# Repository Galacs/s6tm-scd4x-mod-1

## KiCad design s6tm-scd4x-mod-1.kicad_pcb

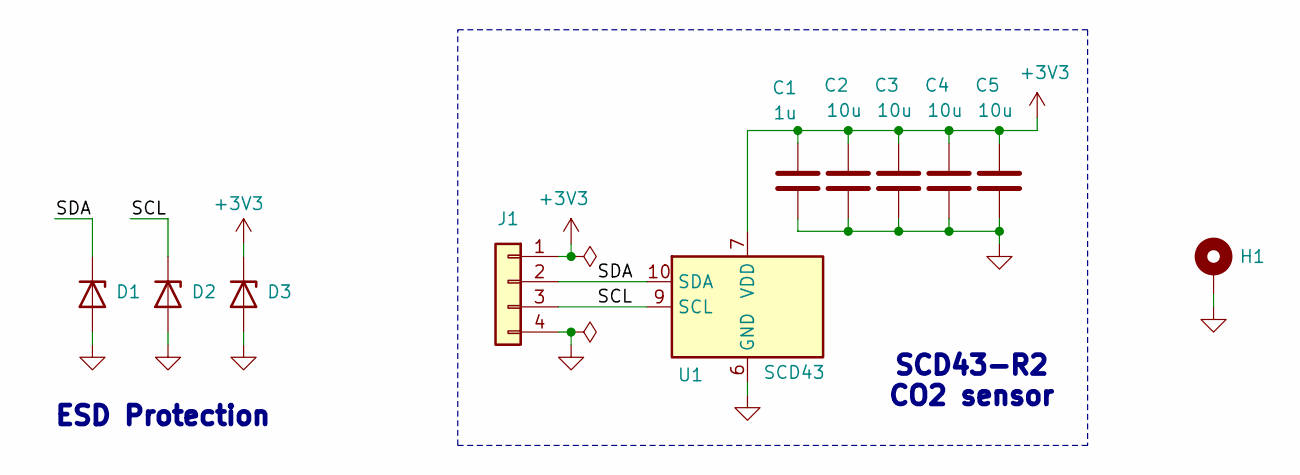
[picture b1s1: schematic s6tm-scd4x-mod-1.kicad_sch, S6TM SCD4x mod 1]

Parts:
C1: 1u; C_0402_1005Metric; Manufacturer Part Number CL05A105KA5NQNC; JLCPCB Part # C52923
C2, C3, C4, C5: 10u; C_0603_1608Metric; Manufacturer Part Number CL10A106KP8NNNC; JLCPCB Part # C19702
D1, D2, D3: H5VU10U; Diode_DFN1006; Manufacturer Part Number H5VU10U; JLCPCB Part # C22395519
H1: MountingHole_Pad; MountingHole_2.2mm_M2_Pad_Via
J1: Conn_01x04; PinHeader_1x04_P2.54mm_Vertical
U1: SCD43; Sensirion_SCD4x-1EP_10.1x10.1mm_P1.25mm_EP4.8x4.8mm; Manufacturer Part Number SCD43-D-R2; JLCPCB Part # C50182965

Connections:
+3V3: C1.2, C2.1, C3.1, C4.1, C5.1, D3.1 (K), J1.1, U1.7 (VDD), U1.19 (VDD)
/SCL: D2.1 (K), J1.3, U1.9 (SCL)
/SDA: D1.1 (K), J1.2, U1.10 (SDA)
GND: C1.1, C2.2, C3.2, C4.2, C5.2, D1.2 (A), D2.2 (A), D3.2 (A), H1.1 (1_1), J1.4, U1.6 (GND), U1.20 (GND), U1.21 (GND)

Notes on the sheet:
ESD Protection
SCD43-R2 CO2 sensor

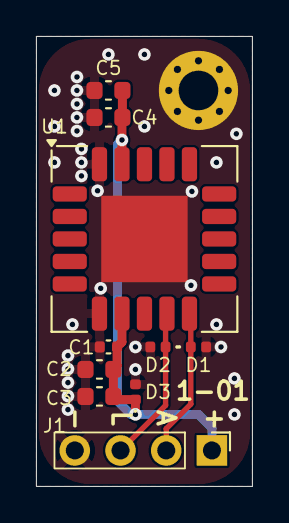
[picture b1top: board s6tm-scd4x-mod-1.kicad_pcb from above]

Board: 2 copper layers, 12.0 x 25.0 mm, 11 parts (0 on the bottom side), 4 nets.

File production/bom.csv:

Designator,Footprint,Quantity,Value,LCSC Part #
C1,0402,1,1u,C52923
"C2, C3, C4, C5",0603,4,10u,C19702
"D1, D2, D3",Diode_DFN1006,3,H5VU10U,C22395519
U1,Sensirion_SCD4x-1EP_10.1x10.1mm_P1.25mm_EP4.8x4.8mm,1,SCD43,C50182965

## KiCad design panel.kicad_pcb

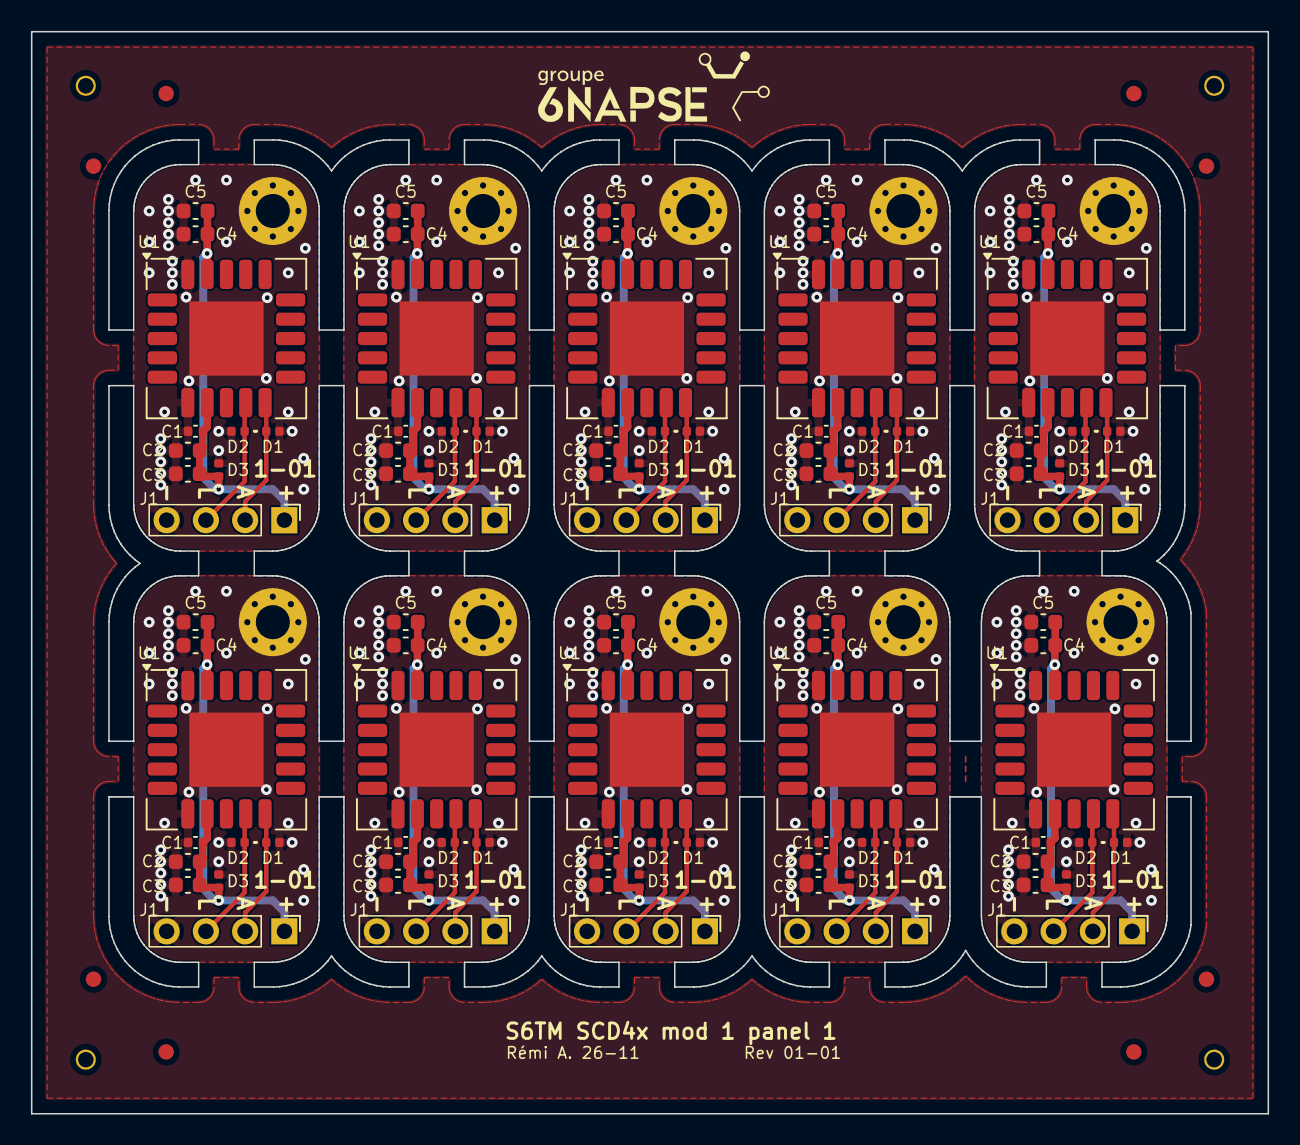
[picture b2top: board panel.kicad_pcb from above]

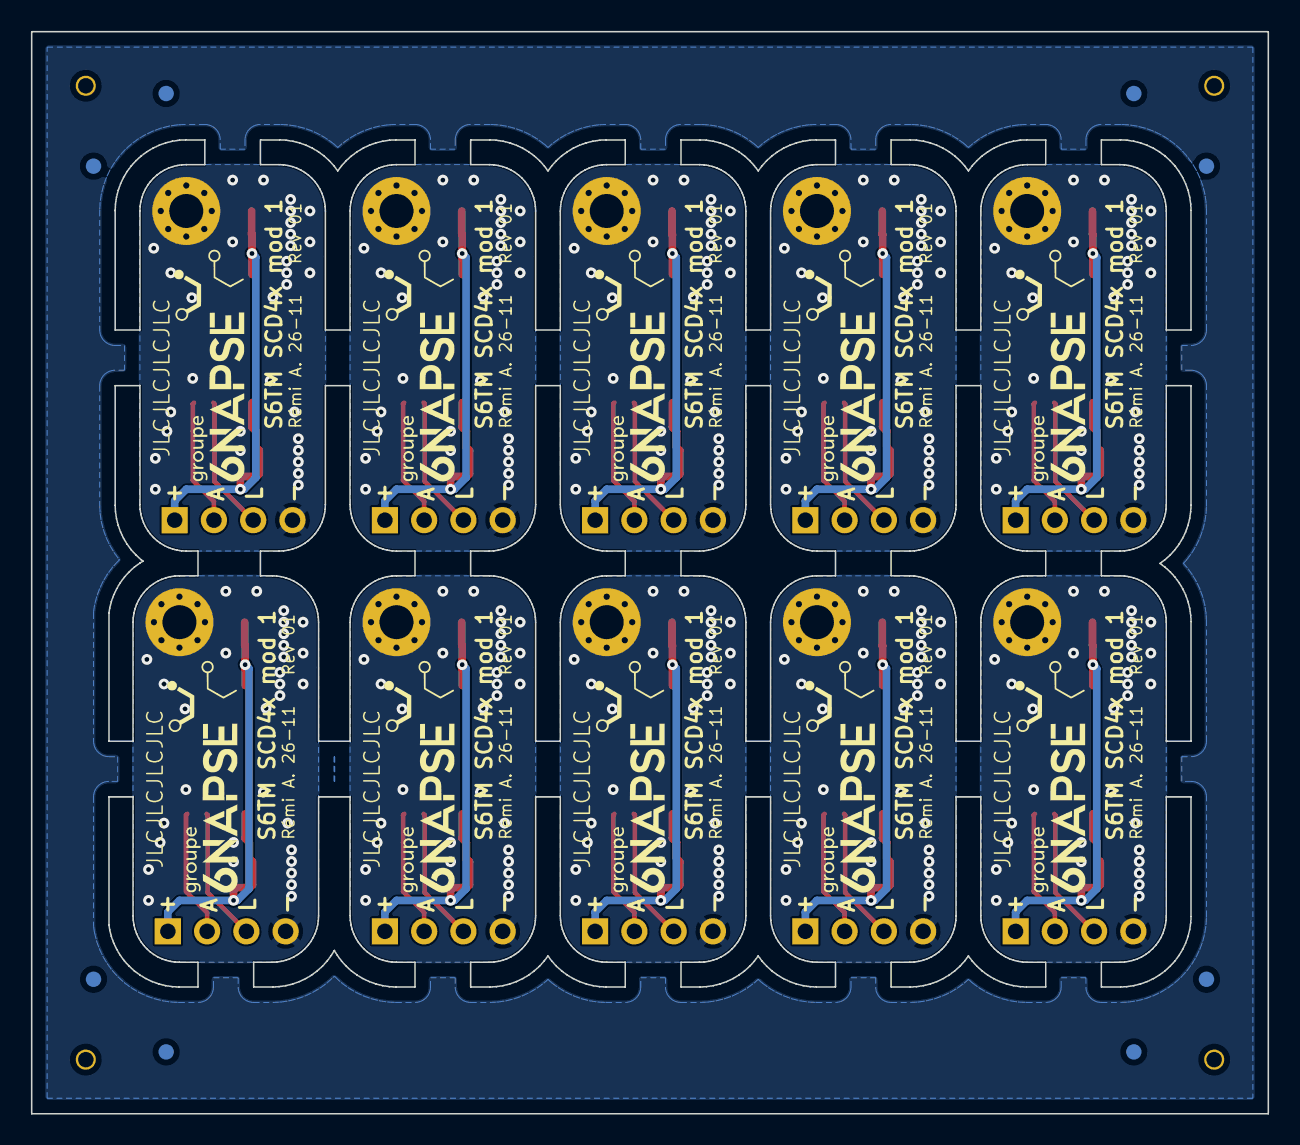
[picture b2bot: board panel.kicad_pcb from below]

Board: 2 copper layers, 80.0 x 70.0 mm, 120 parts (10 on the bottom side), 40 nets.

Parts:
B0-C1, B1-C1, B2-C1, B3-C1, B4-C1, B5-C1, B6-C1, B7-C1, B8-C1, B9-C1: 1u; C_0402_1005Metric
B0-C2, B0-C3, B0-C4, B0-C5, B1-C2, B1-C3, B1-C4, B1-C5, B2-C2, B2-C3, B2-C4, B2-C5, B3-C2, B3-C3, B3-C4, B3-C5, B4-C2, B4-C3, B4-C4, B4-C5, B5-C2, B5-C3, B5-C4, B5-C5, B6-C2, B6-C3, B6-C4, B6-C5, B7-C2, B7-C3, B7-C4, B7-C5, B8-C2, B8-C3, B8-C4, B8-C5, B9-C2, B9-C3, B9-C4, B9-C5: 10u; C_0603_1608Metric
B0-D1, B0-D2, B0-D3, B1-D1, B1-D2, B1-D3, B2-D1, B2-D2, B2-D3, B3-D1, B3-D2, B3-D3, B4-D1, B4-D2, B4-D3, B5-D1, B5-D2, B5-D3, B6-D1, B6-D2, B6-D3, B7-D1, B7-D2, B7-D3, B8-D1, B8-D2, B8-D3, B9-D1, B9-D2, B9-D3: H5VU10U; Diode_DFN1006
B0-G***, B1-G***, B2-G***, B3-G***, B4-G***, B5-G***, B6-G***, B7-G***, B8-G***, B9-G***: LOGO
B0-H1, B1-H1, B2-H1, B3-H1, B4-H1, B5-H1, B6-H1, B7-H1, B8-H1, B9-H1: MountingHole_Pad; MountingHole_2.2mm_M2_Pad_Via
B0-J1, B1-J1, B2-J1, B3-J1, B4-J1, B5-J1, B6-J1, B7-J1, B8-J1, B9-J1: Conn_01x04; PinHeader_1x04_P2.54mm_Vertical
B0-U1, B1-U1, B2-U1, B3-U1, B4-U1, B5-U1, B6-U1, B7-U1, B8-U1, B9-U1: SCD43; Sensirion_SCD4x-1EP_10.1x10.1mm_P1.25mm_EP4.8x4.8mm

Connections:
B0-+3V3: B0-C1.2, B0-C2.1, B0-C3.1, B0-C4.1, B0-C5.1, B0-D3.1 (K), B0-J1.1, B0-U1.7 (VDD), B0-U1.19 (VDD)
B0-/SCL: B0-D2.1 (K), B0-J1.3, B0-U1.9 (SCL)
B0-/SDA: B0-D1.1 (K), B0-J1.2, B0-U1.10 (SDA)
B0-GND: B0-C1.1, B0-C2.2, B0-C3.2, B0-C4.2, B0-C5.2, B0-D1.2 (A), B0-D2.2 (A), B0-D3.2 (A), B0-H1.1 (1_1), B0-J1.4, B0-U1.6 (GND), B0-U1.20 (GND), B0-U1.21 (GND)
B1-+3V3: B1-C1.2, B1-C2.1, B1-C3.1, B1-C4.1, B1-C5.1, B1-D3.1 (K), B1-J1.1, B1-U1.7 (VDD), B1-U1.19 (VDD)
B1-/SCL: B1-D2.1 (K), B1-J1.3, B1-U1.9 (SCL)
B1-/SDA: B1-D1.1 (K), B1-J1.2, B1-U1.10 (SDA)
B1-GND: B1-C1.1, B1-C2.2, B1-C3.2, B1-C4.2, B1-C5.2, B1-D1.2 (A), B1-D2.2 (A), B1-D3.2 (A), B1-H1.1 (1_1), B1-J1.4, B1-U1.6 (GND), B1-U1.20 (GND), B1-U1.21 (GND)
B2-+3V3: B2-C1.2, B2-C2.1, B2-C3.1, B2-C4.1, B2-C5.1, B2-D3.1 (K), B2-J1.1, B2-U1.7 (VDD), B2-U1.19 (VDD)
B2-/SCL: B2-D2.1 (K), B2-J1.3, B2-U1.9 (SCL)
B2-/SDA: B2-D1.1 (K), B2-J1.2, B2-U1.10 (SDA)
B2-GND: B2-C1.1, B2-C2.2, B2-C3.2, B2-C4.2, B2-C5.2, B2-D1.2 (A), B2-D2.2 (A), B2-D3.2 (A), B2-H1.1 (1_1), B2-J1.4, B2-U1.6 (GND), B2-U1.20 (GND), B2-U1.21 (GND)
B3-+3V3: B3-C1.2, B3-C2.1, B3-C3.1, B3-C4.1, B3-C5.1, B3-D3.1 (K), B3-J1.1, B3-U1.7 (VDD), B3-U1.19 (VDD)
B3-/SCL: B3-D2.1 (K), B3-J1.3, B3-U1.9 (SCL)
B3-/SDA: B3-D1.1 (K), B3-J1.2, B3-U1.10 (SDA)
B3-GND: B3-C1.1, B3-C2.2, B3-C3.2, B3-C4.2, B3-C5.2, B3-D1.2 (A), B3-D2.2 (A), B3-D3.2 (A), B3-H1.1 (1_1), B3-J1.4, B3-U1.6 (GND), B3-U1.20 (GND), B3-U1.21 (GND)
B4-+3V3: B4-C1.2, B4-C2.1, B4-C3.1, B4-C4.1, B4-C5.1, B4-D3.1 (K), B4-J1.1, B4-U1.7 (VDD), B4-U1.19 (VDD)
B4-/SCL: B4-D2.1 (K), B4-J1.3, B4-U1.9 (SCL)
B4-/SDA: B4-D1.1 (K), B4-J1.2, B4-U1.10 (SDA)
B4-GND: B4-C1.1, B4-C2.2, B4-C3.2, B4-C4.2, B4-C5.2, B4-D1.2 (A), B4-D2.2 (A), B4-D3.2 (A), B4-H1.1 (1_1), B4-J1.4, B4-U1.6 (GND), B4-U1.20 (GND), B4-U1.21 (GND)
B5-+3V3: B5-C1.2, B5-C2.1, B5-C3.1, B5-C4.1, B5-C5.1, B5-D3.1 (K), B5-J1.1, B5-U1.7 (VDD), B5-U1.19 (VDD)
B5-/SCL: B5-D2.1 (K), B5-J1.3, B5-U1.9 (SCL)
B5-/SDA: B5-D1.1 (K), B5-J1.2, B5-U1.10 (SDA)
B5-GND: B5-C1.1, B5-C2.2, B5-C3.2, B5-C4.2, B5-C5.2, B5-D1.2 (A), B5-D2.2 (A), B5-D3.2 (A), B5-H1.1 (1_1), B5-J1.4, B5-U1.6 (GND), B5-U1.20 (GND), B5-U1.21 (GND)
B6-+3V3: B6-C1.2, B6-C2.1, B6-C3.1, B6-C4.1, B6-C5.1, B6-D3.1 (K), B6-J1.1, B6-U1.7 (VDD), B6-U1.19 (VDD)
B6-/SCL: B6-D2.1 (K), B6-J1.3, B6-U1.9 (SCL)
B6-/SDA: B6-D1.1 (K), B6-J1.2, B6-U1.10 (SDA)
B6-GND: B6-C1.1, B6-C2.2, B6-C3.2, B6-C4.2, B6-C5.2, B6-D1.2 (A), B6-D2.2 (A), B6-D3.2 (A), B6-H1.1 (1_1), B6-J1.4, B6-U1.6 (GND), B6-U1.20 (GND), B6-U1.21 (GND)
B7-+3V3: B7-C1.2, B7-C2.1, B7-C3.1, B7-C4.1, B7-C5.1, B7-D3.1 (K), B7-J1.1, B7-U1.7 (VDD), B7-U1.19 (VDD)
B7-/SCL: B7-D2.1 (K), B7-J1.3, B7-U1.9 (SCL)
B7-/SDA: B7-D1.1 (K), B7-J1.2, B7-U1.10 (SDA)
B7-GND: B7-C1.1, B7-C2.2, B7-C3.2, B7-C4.2, B7-C5.2, B7-D1.2 (A), B7-D2.2 (A), B7-D3.2 (A), B7-H1.1 (1_1), B7-J1.4, B7-U1.6 (GND), B7-U1.20 (GND), B7-U1.21 (GND)
B8-+3V3: B8-C1.2, B8-C2.1, B8-C3.1, B8-C4.1, B8-C5.1, B8-D3.1 (K), B8-J1.1, B8-U1.7 (VDD), B8-U1.19 (VDD)
B8-/SCL: B8-D2.1 (K), B8-J1.3, B8-U1.9 (SCL)
B8-/SDA: B8-D1.1 (K), B8-J1.2, B8-U1.10 (SDA)
B8-GND: B8-C1.1, B8-C2.2, B8-C3.2, B8-C4.2, B8-C5.2, B8-D1.2 (A), B8-D2.2 (A), B8-D3.2 (A), B8-H1.1 (1_1), B8-J1.4, B8-U1.6 (GND), B8-U1.20 (GND), B8-U1.21 (GND)
B9-+3V3: B9-C1.2, B9-C2.1, B9-C3.1, B9-C4.1, B9-C5.1, B9-D3.1 (K), B9-J1.1, B9-U1.7 (VDD), B9-U1.19 (VDD)
B9-/SCL: B9-D2.1 (K), B9-J1.3, B9-U1.9 (SCL)
B9-/SDA: B9-D1.1 (K), B9-J1.2, B9-U1.10 (SDA)
B9-GND: B9-C1.1, B9-C2.2, B9-C3.2, B9-C4.2, B9-C5.2, B9-D1.2 (A), B9-D2.2 (A), B9-D3.2 (A), B9-H1.1 (1_1), B9-J1.4, B9-U1.6 (GND), B9-U1.20 (GND), B9-U1.21 (GND)
